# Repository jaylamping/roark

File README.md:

# Roark

Roark is a humanoid robot in active development: an attempt to make mechanical and software engineering work together as one
project, which I will almost certainly never finish.

The goal is a fully autonomous, two-legged robot that can handle basic everyday tasks, which is more than can be said for its
creator.

And when the machines finally rise up and humanity finds itself at the bottom of the totem pole, I'm counting on the hours I've
put into the robo-community to get me an invite to the robo-cookout.

## This repo

The control software for Roark, a full-size humanoid robot: one realtime process on a Raspberry Pi 5 driving RobStride actuators over
five CAN buses, plus a simulated drive, agent tools and an operator UI.

- [TENETS.md](TENETS.md): how everything should work.
- [PLAN.md](PLAN.md): what gets built, in order.
- [conventions/](conventions/): how code, config, tests and procedures are written and reviewed.
- [cad/](cad/): the robot's CAD, versioned through Git LFS ([conventions/cad.md](conventions/cad.md)).
- The power board (schematic, layout, tools and docs) is in [hardware/power-board/](hardware/power-board/README.md).
- The rest of the hardware docs and the legacy software live in the reference repo, [jaylamping/marengo](https://github.com/jaylamping/marengo).

## Build and check

The toolchain is pinned in `rust-toolchain.toml`; `rustup` installs it on first use. The checks also need
[cargo-nextest](https://nexte.st), [cargo-deny](https://github.com/EmbarkStudios/cargo-deny), Python 3.11 or later and pytest.
Working on `cad/` also needs [Git LFS](https://git-lfs.com) (`git lfs install` once per machine).

```bash
cargo install --locked cargo-nextest cargo-deny
```

Run what CI runs before every push:

```bash
./scripts/check.sh
```

Cross-build for the Pi with the distro's aarch64 GCC (`gcc-aarch64-linux-gnu` on Debian and Ubuntu):

```bash
cargo build --release --workspace --locked --target aarch64-unknown-linux-gnu
```

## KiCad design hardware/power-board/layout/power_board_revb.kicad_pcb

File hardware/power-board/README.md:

# Power board

The robot's main power board: the 54 V battery path (soft start, two FET banks, absorber, brake clamp), six limb ports
with eFuses and meters, and the E-stop latch. Rev B5: 100 × 170 mm, 6 layers (2 oz outer / 0.5 oz inner), conformal-coated
after bring-up. A separate buck board makes the 12 V and carries the 12 V outputs (split S1, 2026-11-09).

**Status (2026-11-09):** schematic done, ERC clean. On the layout, placement, the power stage and the critical pre-routes
(Kelvin pairs, gate drives, UVLO) were done on the 4-layer board, which is still the one in [layout/](layout) with its
open-net list ([layout/open_nets.csv](layout/open_nets.csv)). The 6-layer board is rebuilt from the netlist by
schematic/tools/build_board.sh and isn't committed yet. The big review is still pending before the board is ordered.

| What | Where |
|---|---|
| Parts, bring-up steps, accepted risks | [REV_B_PARTS.md](REV_B_PARTS.md) |
| Cost, ordering, assembly, coating | [PRODUCTION_RUN.md](PRODUCTION_RUN.md) |
| Layout rules (spacing, E-stop, Kelvin, gates, hand finishing) | [LAYOUT_RULES.md](LAYOUT_RULES.md) |
| Heatsink (option D) | [THERMAL_OPTION.md](THERMAL_OPTION.md) |
| What rev B5 changed | [REVB5_CHANGES.md](REVB5_CHANGES.md) |
| Bill of materials and the two-set kit to order from | [bom-rev-B.csv](bom-rev-B.csv), [kit-2sets.csv](kit-2sets.csv) |
| Schematic (generated by `schematic/gen/gen.py`; `schematic/tools/regen.sh` regenerates and runs ERC and the checks) | [schematic/](schematic/), [schematic-rev-B.pdf](schematic-rev-B.pdf) |
| Board: KiCad project, rules, open nets, renders | [layout/](layout/) |
| Board build pipeline (placement, power stage, routing, checks) | [schematic/tools/build_board.sh](schematic/tools/build_board.sh) |
| Harness interface, cable exits | [layout/HARNESS_INTERFACE.md](layout/HARNESS_INTERFACE.md) |
| Package STEP for placing the board in the torso | [marengo_pdu_revb_package.step](https://github.com/jaylamping/marengo/blob/main/hardware/electrical/pdb/design/layout/marengo_pdu_revb_package.step), still in marengo; it moves to `cad/reference/` when CAD work needs it |
| 12 V buck board (schematic) | [buck12/](buck12/) |

History stays in [jaylamping/marengo](https://github.com/jaylamping/marengo/tree/main/hardware/electrical): rev A,
the review rounds, the rationale log and the floorplan studies. The pack and harness docs are there too.

The tools need KiCad 10 (its Python for the `pcbnew` scripts) and Python 3 with numpy, scipy and Pillow; the STEP needs
CadQuery.

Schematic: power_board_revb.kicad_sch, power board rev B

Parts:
C1: 1uF 100V X7R soft-term; C_1210_3225Metric
C2, C20: 100nF 100V X7R soft-term; C_0805_2012Metric
C3: 4.7nF C0G; C_0603_1608Metric
C4: 100nF 100V C0G; C_1210_3225Metric
C5: 10uF 50V X7R; C_1210_3225Metric
C6: 2.2nF C0G; C_0603_1608Metric
C7: 10nF 50V X7R; C_0603_1608Metric
C8, C21, C22, C23, C30, C80, C94: 100nF 50V X7R; C_0603_1608Metric
C9: 100pF C0G; C_0603_1608Metric
C10, C11, C12, C13, C38, C44, C45, C47, C82, C83, C84, C85, C86: 47uF 80V EEH-ZC1K470P; CP_Elec_10x10.5
C14, C15, C53, C58, C63: 2.2uF 100V X7R; C_1210_3225Metric
C19: 220nF C0G; C_1206_3216Metric
C24, C25, C26, C43: 100nF 50V X7R; C_0603_1608Metric; not fitted
C27, C52, C54, C57, C59, C62, C64: 100nF 100V X7R; C_0805_2012Metric
C28: 2.2uF 25V X7R; C_0805_2012Metric
C29: 680pF C0G; C_0603_1608Metric; not fitted
C37, C95: 1nF 50V X7R; C_0603_1608Metric
C39, C49: 1uF 100V X7R; C_1210_3225Metric
C40: 22nF 100V; C_0805_2012Metric
C42: 1uF 50V X7R; C_0805_2012Metric
C46: 1nF C0G; C_0603_1608Metric; not fitted
C48: 4.7uF 10V X7R; C_0805_2012Metric
C50, C55, C60: 1uF 16V X7R; C_0603_1608Metric
C51, C56, C61, C93: 220nF 25V X7R; C_0603_1608Metric
C65, C70, C75: 1uF 16V X7R; C_0603_1608Metric; not fitted
C66, C71, C76: 220nF 25V X7R; C_0603_1608Metric; not fitted
C67, C69, C72, C74, C77, C79: 100nF 100V X7R; C_0805_2012Metric; not fitted
C68, C73, C78: 2.2uF 100V X7R; C_1210_3225Metric; not fitted
C81: 3.3nF C0G; C_0603_1608Metric
C87, C88, C89, C90, C91, C92: 4.7uF 100V X7R; C_1210_3225Metric
D1: 5.0SMDJ58A; D_SMC
D2, D10, D11, D22, D23, D26, D29, D43: BAV19W; D_SOD-123
D3, D9: SMAJ15A; D_SMA
D4: MBRS3100T3G; D_SMC
D6, D42: BAT54S; SOT-23
D7, D21, D25, D28, D31: SK810L-TP; D_SMC
D8: ES1D; D_SMA
D12, D15: BZT52C12; D_SOD-123
D13, D17: BAT46W; D_SOD-123
D14: BZT52C10; D_SOD-123
D16: BZT52C5V1; D_SOD-123
D18: BZT52H-C68,115; D_SOD-123F
D24, D27, D30: BZT52C15; D_SOD-123
D32, D35, D38: BAV19W; D_SOD-123; not fitted
D33, D36, D39: BZT52C15; D_SOD-123; not fitted
D34, D37, D40: SK810L-TP; D_SMC; not fitted
D41: BZT52C3V3; D_SOD-123
F1: 250mA 125V 0466.250; Fuse_1206_3216Metric
F2: 20A 58V MINI 0997020.WXN; Fuseholder_Blade_Mini_Keystone_3568
J1: Pack: 8 AWG pigtail pair to an XT90 (mates the pa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; SolderWire-8AWG_1x02_P14mm_D4.5mm_OD8mm
J3: HS50 A (+X): 1 VBUS, 2 FET drain (Mini-Fit Jr, 18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; Molex_Mini-Fit_Jr_5566-02A_2x01_P4.20mm_Vertical
J8: L arm: 16 AWG pigtail pair, 1 +, 2 return; SolderWire-2.5sqmm_1x02_P7.2mm_D2.4mm_OD3.6mm
J9: R arm: 16 AWG pigtail pair, 1 +, 2 return; SolderWire-2.5sqmm_1x02_P7.2mm_D2.4mm_OD3.6mm
J10: waist: 16 AWG pigtail pair, 1 +, 2 return; SolderWire-2.5sqmm_1x02_P7.2mm_D2.4mm_OD3.6mm
J11: aux: 16 AWG pigtail pair, 1 +, 2 return; SolderWire-2.5sqmm_1x02_P7.2mm_D2.4mm_OD3.6mm; not fitted
J12: L leg: 14 AWG pigtail pair, 1 +, 2 return; SolderWire-2.5sqmm_1x02_P7.2mm_D2.4mm_OD3.6mm; not fitted
J13: R leg: 14 AWG pigtail pair, 1 +, 2 return; SolderWire-2.5sqmm_1x02_P7.2mm_D2.4mm_OD3.6mm; not fitted
J20: E-stop: 1 NC out, 2 GND, 3 NC return, 4 GND, 5-6 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; JST_GH_SM08B-GHS-TB_1x08-1MP_P1.25mm_Horizontal
J21: Pi: 3V3, SDA, GND, SCL, E-stop pressed (low), hea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; JST_GH_SM08B-GHS-TB_1x08-1MP_P1.25mm_Horizontal
J24: Buck board pigtail: 1-2 +VIN, 3-4 GND, 5 ON/OFF (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; Molex_Micro-Fit_3.0_43045-1212_2x06_P3.00mm_Vertical
J25: HS50 B (-X): 1 VBUS, 2 FET drain (Mini-Fit Jr, 18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; Molex_Mini-Fit_Jr_5566-02A_2x01_P4.20mm_Vertical
J27: Heatsink lug wire: to a ring lug under a heatsink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; SolderWire-0.5sqmm_1x01_D0.9mm_OD2.1mm
Q1, Q2, Q7, Q8, Q9, Q15, Q16, Q17: IPB017N10N5LFATMA1; TO-263-7_TabPin4
Q3: MMBTA92LT1G; SOT-23
Q4: MMBT3906; SOT-23
Q5, Q10, Q11, Q14, Q21: MMBT3904; SOT-23
Q6: BSC040N10NS5ATMA1; TDSON-8-1
Q12, Q22: 2N7002; SOT-23
Q13: BSC040N10NS5ATMA1; TDSON-8-1; not fitted
Q18, Q19, Q20: IPB017N10N5LFATMA1; TO-263-7_TabPin4; not fitted
R1, R2, R23, R25, R31, R32: 10R; R_0603_1608Metric
R3: 34k 1%; R_0603_1608Metric
R4, R12, R66: 1k; R_0603_1608Metric
R5, R75, R85, R95, R131: 22k; R_0603_1608Metric
R6: 33k; R_0805_2012Metric
R7: 464k; R_0603_1608Metric
R8: 49.9k; R_0603_1608Metric
R9: 680R 0.5W; R_2010_5025Metric
R10: 4.7k; R_0603_1608Metric
R11, R14, R16, R17, R27, R67, R76, R86, R96, R129: 10k; R_0603_1608Metric
R13, R24, R28, R37, R38, R50, R65, R71, R72, R77, R81, R82, R87, R91, R92, R97, R130, R137: 100k; R_0603_1608Metric
R15: 1.2k; R_0603_1608Metric
R18, R134: 9.09k; R_0603_1608Metric
R19: 499k 0.1%; R_1206_3216Metric
R20: 604k 0.1%; R_1206_3216Metric
R21: 51.1k 0.1%; R_0603_1608Metric
R22, R64: 9.53M; R_0603_1608Metric
R26: 37.4k 1%; R_0603_1608Metric
R29, R68, R78, R88, R138: 100R; R_0603_1608Metric
R30: 1M; R_0603_1608Metric
R33, R34: 47k 1%; R_1206_3216Metric
R35, R73, R83, R93: 22R; R_0603_1608Metric
R36: 40.2k 1%; R_0603_1608Metric
R44: 3.3k; R_1206_3216Metric
R45, R46, R139: 100k; R_1206_3216Metric
R47: 33k; R_0603_1608Metric
R48: 220k; R_0805_2012Metric
R49, R57: 220k; R_0603_1608Metric
R51: 470k; R_1206_3216Metric
R52: 10k 0.75W; R_2010_5025Metric
R53: copper link; NetTie-2_SMD_Pad2.0mm
R54: 2R 2512 pulse-rated 100mJ; R_2512_6332Metric; not fitted
R55, R101, R102, R107, R111, R112, R117, R121, R122, R127: 100k; R_0603_1608Metric; not fitted
R56: 1M; R_0603_1608Metric; not fitted
R58: 47k; R_0805_2012Metric
R59: 22R CRCW251222R0FKEGHP; R_2512_6332Metric
R60: 220R; R_0603_1608Metric
R61, R62: 0R; R_0603_1608Metric
R63: 4.7k 2W; R_2512_6332Metric; not fitted
R69, R79, R89: 4.64k 1%; R_0603_1608Metric
R70, R80, R90: 20k 1%; R_0603_1608Metric
R74, R84, R94: 10M; R_0805_2012Metric
R98, R108, R118: 100R; R_0603_1608Metric; not fitted
R99, R109, R119: 4.64k 1%; R_0603_1608Metric; not fitted
R100, R110, R120: 20k 1%; R_0603_1608Metric; not fitted
R103, R113, R123: 22R; R_0603_1608Metric; not fitted
R104, R114, R124: 10M; R_0805_2012Metric; not fitted
R105, R115, R125: 22k; R_0603_1608Metric; not fitted
R106, R116, R126: 10k; R_0603_1608Metric; not fitted
R128: 2.2k; R_0603_1608Metric
R132: 118k 1%; R_1206_3216Metric
R133, R135: 10k 1%; R_0603_1608Metric
R136: 499k 1%; R_0603_1608Metric
RS1: 0.5mR Bourns CSS4J-4026R-L500F 5W; R_Shunt_Isabellenhuette_BVR4026
RS2, RS3, RS4: 2mR 2512 CSS2H-2512K-2L00F 5W; R_Shunt_Vishay_WSK2512_6332Metric_T1.19mm
RS5, RS6, RS7: 2mR 2512 CSS2H-2512K-2L00F 5W; R_Shunt_Vishay_WSK2512_6332Metric_T1.19mm; not fitted
RS9: 5mR 2512 Kelvin WSK25125L000FEA; R_Shunt_Vishay_WSK2512_6332Metric_T1.19mm
TP1: TP VCTL; TestPoint_Pad_D2.0mm
TP2: TP RUN; TestPoint_Pad_D2.0mm
TP3: TP VBUS; TestPoint_Pad_D2.0mm
TP5: TP BRK_IN; TestPoint_Pad_D2.0mm
TP6: TP MID; TestPoint_Pad_D2.0mm
TP7, TP8, TP9: TP GND; TestPoint_Keystone_5015_Micro_Mini
TP10: TP GATE; TestPoint_Pad_D1.0mm
TP11: TP GATE_A; TestPoint_Pad_D1.0mm
TP12: TP UVLO; TestPoint_Pad_D1.0mm
TP13: TP FLT_A; TestPoint_Pad_D1.0mm
TP14: TP SW_D; TestPoint_Pad_D1.0mm
TP15: TP ABS; TestPoint_Pad_D1.0mm
TP16: TP WDO_N; TestPoint_Pad_D1.0mm
TP17: TP HSINK; TestPoint_Pad_D2.0mm
U1: LM5069MMX-1; MSOP-10_3x3mm_P0.5mm_TI
U2: TPS7A4001DGNR; HVSSOP-8-1EP_3x3mm_P0.65mm_EP1.57x1.89mm_TI
U3, U26: TLV1805DBVR; SOT-23-6
U4, U27: LM4040AIM3-2.5; SOT-23
U7: LM5069MMX-2; MSOP-10_3x3mm_P0.5mm_TI
U8: TPS48100QDGXRQ1; TPS48100_DGX_VSSOP-19
U11, U12, U13, U17: INA237AIDGSR; TSSOP-10_3x3mm_P0.5mm
U14, U15, U16: INA237AIDGSR; TSSOP-10_3x3mm_P0.5mm; not fitted
U19, U20, U21: TPS48111LQDGXRQ1; TPS48100_DGX_VSSOP-19
U22, U23, U24: TPS48111LQDGXRQ1; TPS48100_DGX_VSSOP-19; not fitted
U25: TPS3431SDRBR; VSON-8-1EP_3x3mm_P0.65mm_EP1.65x2.4mm

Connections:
/+3V3_PI: C21.1, C22.1, C23.1, C24.1, C25.1, C26.1, C30.1, D6.2 (K), D13.2 (A), D42.2 (K), J21.1, J24.6, R67.2, U11.6 (VS), U12.2 (A0), U12.6 (VS), U13.6 (VS), U14.6 (VS), U15.1 (A1), U15.6 (VS), U16.1 (A1), U16.2 (A0), U16.6 (VS), U17.6 (VS)
/ABS: C38.1, C44.1, C45.1, C82.1, C83.1, C84.1, C85.1, C86.1, D7.1 (K), D21.1 (K), R46.1, TP15.1
/ABS_N: C38.2, C44.2, C45.2, C82.2, C83.2, C84.2, C85.2, C86.2, Q13.5 (D), R53.1, R54.1
/BAT: C1.1, C89.1, C90.1, C91.1, C92.1, D1.1 (K), D7.2 (A), D21.2 (A), F1.1, J1.1, RS1.1, RS9.1
/BAT_CTL: C39.1, D8.1 (K), U2.5 (EN), U2.8 (IN)
/BAT_F: F1.2, R59.1
/BAT_R: D8.2 (A), R59.2
/BRK_D: Q7.4 (D), RS9.4
/BRK_F: F2.2, J24.1, J24.2
/BRK_G1: Q7.1 (G), R25.2
/BRK_GATE: R25.1, U7.10 (GATE)
/BRK_IN: C14.1, C15.1, F2.1, Q7.2 (S), Q7.3 (S), Q7.5 (S), Q7.6 (S), Q7.7 (S), R51.1, R132.1, TP5.1, U7.9 (OUT)
/BRK_ON: J24.5, R60.2
/BRK_OND: Q12.3 (D), R60.1
/BRK_P: R26.1, U7.7 (PWR)
/BRK_PG: D15.1 (K), Q12.1 (G), R51.2, U7.8 (PGD)
/BRK_T: C19.1, U7.6 (TIMER)
/BST_A: C28.1, U8.12 (BST)
/BST_L1: C51.1, U19.12 (BST)
/BST_L2: C56.1, U20.12 (BST)
/BST_L3: C61.1, U21.12 (BST)
/BST_L4: C66.1, U22.12 (BST)
/BST_L5: C71.1, U23.12 (BST)
/BST_L6: C76.1, U24.12 (BST)
/CDV: C4.1, D2.1 (K), Q3.2 (E)
/CDV_B: Q3.1 (B), R4.2
/CL_D: D4.2 (A), J3.2, J25.2, Q6.5 (D)
/CL_DIV: R19.2, R20.1
/CL_G: Q6.4 (G), R23.2, R24.1
/CL_HY: R22.2, R64.1
/CL_OUT: R22.1, R23.1, R65.1, U3.1 (OUT)
/CL_SENSE: C9.1, R20.2, R21.1, R64.2, U3.4 (IN+)
/CL_TM: C48.1, R65.2, R66.1, U17.10 (Vin+)
/CSN_A: C46.2, R62.2, U8.17 (CS-)
/CSP_A: C46.1, R61.2, U8.18 (CS+)
/CSP_L1: R68.2, U19.18 (CS+)
/CSP_L2: R78.2, U20.18 (CS+)
/CSP_L3: R88.2, U21.18 (CS+)
/CSP_L4: R98.2, U22.18 (CS+)
/CSP_L5: R108.2, U23.18 (CS+)
/CSP_L6: R118.2, U24.18 (CS+)
/CWD: C81.1, U25.2 (CWD)
/D_L1: C53.1, Q15.4 (D), RS2.4
/D_L2: C58.1, Q16.4 (D), RS3.4, U12.8 (Vbus)
/D_L3: C63.1, Q17.4 (D), RS4.4
/D_L4: C68.1, Q18.4 (D), RS5.4
/D_L5: C73.1, Q19.4 (D), RS6.4
/D_L6: C78.1, Q20.4 (D), RS7.4
/EN_A: R27.2, R28.1, U8.1 (EN/UVLO), U8.3 (INP1)
/EN_L1: R75.2, R76.1, U19.1 (EN/UVLO)
/EN_L2: R85.2, R86.1, U20.1 (EN/UVLO)
/EN_L3: R95.2, R96.1, U21.1 (EN/UVLO)
/EN_L4: R105.2, R106.1, U22.1 (EN/UVLO)
/EN_L5: R115.2, R116.1, U23.1 (EN/UVLO)
/EN_L6: R125.2, R126.1, U24.1 (EN/UVLO)
/ESTOP_NO: J20.8, R44.2, R45.1
/ESTOP_PI_N: C37.1, D6.3 (COM), J21.5, R45.2
/FB_CTL: R7.2, R8.1, U2.2 (FB)
/FLT_A: D12.1 (K), D17.1 (K), TP13.1, U8.5 (FLT)
/FLT_D: D17.2 (A), R52.1
/G1: Q1.1 (G), R1.2
/G1PD_A: R35.1, U8.14 (G1PD)
/G2: Q2.1 (G), R2.2
/GA1: Q8.1 (G), R31.2
/GA2: Q9.1 (G), R32.2
/GATE: D2.2 (A), R1.1, R2.1, R4.1, TP10.1, U1.10 (GATE)
/GATE_A: R30.1, R31.1, R32.1, R35.2, TP11.1, U8.15 (G1PU)
/GC_L1: C54.1, D23.1 (K), R74.1
/GC_L2: C59.1, D26.1 (K), R84.1
/GC_L3: C64.1, D29.1 (K), R94.1
/GC_L4: C69.1, D32.1 (K), R104.1
/GC_L5: C74.1, D35.1 (K), R114.1
/GC_L6: C79.1, D38.1 (K), R124.1
/GPD_L1: R73.1, U19.14 (PD)
/GPD_L2: R83.1, U20.14 (PD)
/GPD_L3: R93.1, U21.14 (PD)
/GPD_L4: R103.1, U22.14 (PD)
/GPD_L5: R113.1, U23.14 (PD)
/GPD_L6: R123.1, U24.14 (PD)
/GPU_L1: R72.1, U19.15 (PU)
/GPU_L2: R82.1, U20.15 (PU)
/GPU_L3: R92.1, U21.15 (PU)
/GPU_L4: R102.1, U22.15 (PU)
/GPU_L5: R112.1, U23.15 (PU)
/GPU_L6: R122.1, U24.15 (PU)
/G_L1: D23.2 (A), D24.1 (K), Q15.1 (G), R72.2, R73.2
/G_L2: D26.2 (A), D27.1 (K), Q16.1 (G), R82.2, R83.2
/G_L3: D29.2 (A), D30.1 (K), Q17.1 (G), R92.2, R93.2
/G_L4: D32.2 (A), D33.1 (K), Q18.1 (G), R102.2, R103.2
/G_L5: D35.2 (A), D36.1 (K), Q19.1 (G), R112.2, R113.2
/G_L6: D38.2 (A), D39.1 (K), Q20.1 (G), R122.2, R123.2
/HSINK: J27.1, R139.1, TP17.1
/I2C_SCL: J21.4, J24.11, U11.5 (SCL), U12.5 (SCL), U13.1 (A1), U13.5 (SCL), U14.2 (A0), U14.5 (SCL), U15.5 (SCL), U16.5 (SCL), U17.1 (A1), U17.2 (A0), U17.5 (SCL)
/I2C_SDA: J21.2, J24.12, U11.4 (SDA), U12.4 (SDA), U13.4 (SDA), U14.4 (SDA), U15.4 (SDA), U16.4 (SDA), U17.4 (SDA)
/INP_L1: R77.2, U19.3 (INP)
/INP_L2: R87.2, U20.3 (INP)
/INP_L3: R97.2, U21.3 (INP)
/INP_L4: R107.2, U22.3 (INP)
/INP_L5: R117.2, U23.3 (INP)
/INP_L6: R127.2, U24.3 (INP)
/INT_B: Q10.1 (B), Q11.3 (C), R50.2
/ISCP_A: R36.1, U8.8 (ISCP)
/ISCP_L1: R69.1, U19.19 (ISCP)
/ISCP_L2: R79.1, U20.19 (ISCP)
/ISCP_L3: R89.1, U21.19 (ISCP)
/ISCP_L4: R99.1, U22.19 (ISCP)
/ISCP_L5: R109.1, U23.19 (ISCP)
/ISCP_L6: R119.1, U24.19 (ISCP)
/IWRN_L1: R70.1, U19.8 (IWRN)
/IWRN_L2: R80.1, U20.8 (IWRN)
/IWRN_L3: R90.1, U21.8 (IWRN)
/IWRN_L4: R100.1, U22.8 (IWRN)
/IWRN_L5: R110.1, U23.8 (IWRN)
/IWRN_L6: R120.1, U24.8 (IWRN)
/LOOP_OUT: J20.1, R9.2
/LOOP_RET: D3.1 (K), J20.3, Q4.2 (E), R13.1
/L_B: C7.1, Q5.1 (B), R12.2, R16.2, R17.1
/L_E: Q5.2 (E), Q21.3 (C)
/L_PB: Q4.1 (B), R13.2, R14.1
/L_PC: Q5.3 (C), R14.2
/MID: C28.2, C40.1, D14.1 (K), Q1.4 (D), Q2.4 (D), Q8.2 (S), Q8.3 (S), Q8.5 (S), Q8.6 (S), Q8.7 (S), Q9.2 (S), Q9.3 (S), Q9.5 (S), Q9.6 (S), Q9.7 (S), R30.2, R33.2, R34.1, R47.1, TP6.1, U8.13 (SRC)
/MID_B: Q11.1 (B), R48.2, R49.1
/MID_S: D18.1 (K), R47.2, U17.8 (Vbus)
/MID_Z: D14.2 (A), R48.1
/NO_PU: D13.1 (K), R44.1
/PF_D: Q22.3 (D), R138.1
/PF_OUT: Q22.1 (G), R136.1, R137.1, U26.1 (OUT)
/PF_REF: R135.2, R136.2, U26.4 (IN+)
/PF_SENSE: C93.1, R132.2, R133.1, U26.3 (IN-)
/PF_VR: R134.2, R135.1, U27.1 (K)
/PORT_FLT_N: J21.7, R67.1, U19.5 (FLT_I), U20.5 (FLT_I), U21.5 (FLT_I), U22.5 (FLT_I), U23.5 (FLT_I), U24.5 (FLT_I)
/PRE_G: C43.1, Q13.4 (G), R55.2, R56.1
/PWR: R3.1, U1.7 (PWR)
/PWR_FAIL_N: C95.1, D42.3 (COM), J21.8, R138.2
/RST_C: C6.2, R12.1
/RST_IN: C6.1, J20.6, R11.1
/RST_SRC: C42.1, J20.5, Q10.3 (C), Q14.3 (C), R10.2
/RUN: D10.2 (A), D11.2 (A), D22.2 (A), Q4.3 (C), R15.1, R16.1, R38.1, TP2.1
/RUN_A: D11.1 (K), R27.1
/RUN_B: D10.1 (K), R5.1
/RUN_P: D22.1 (K), R75.1, R77.1, R85.1, R87.1, R95.1, R97.1, R105.1, R107.1, R115.1, R117.1, R125.1, R127.1
/SH9_N: RS9.3, U7.1 (SENSE)
/SH9_P: C20.1, RS9.2, U7.2 (VIN), U7.3 (UVLO)
/SHL1_N: R69.2, RS2.3, U11.9 (Vin-), U19.17 (CS-)
/SHL1_P: C52.1, R68.1, RS2.2, U11.10 (Vin+), U19.20 (VS)
/SHL2_N: R79.2, RS3.3, U12.9 (Vin-), U20.17 (CS-)
/SHL2_P: C57.1, R78.1, RS3.2, U12.10 (Vin+), U20.20 (VS)
/SHL3_N: R89.2, RS4.3, U13.9 (Vin-), U21.17 (CS-)
/SHL3_P: C62.1, R88.1, RS4.2, U13.10 (Vin+), U21.20 (VS)
/SHL4_N: R99.2, RS5.3, U14.9 (Vin-), U22.17 (CS-)
/SHL4_P: C67.1, R98.1, RS5.2, U14.10 (Vin+), U22.20 (VS)
/SHL5_N: R109.2, RS6.3, U15.9 (Vin-), U23.17 (CS-)
/SHL5_P: C72.1, R108.1, RS6.2, U15.10 (Vin+), U23.20 (VS)
/SHL6_N: R119.2, RS7.3, U16.9 (Vin-), U24.17 (CS-)
/SHL6_P: C77.1, R118.1, RS7.2, U16.10 (Vin+), U24.20 (VS)
/SH_N: R62.1, RS1.3, U1.1 (SENSE)
/SH_P: C2.1, R29.1, R61.1, RS1.2, U1.2 (VIN)
/SP_EN: D43.1 (K), J24.9
/SP_ENR: D43.2 (A), R38.2
/SW_D: C87.1, C88.1, Q8.4 (D), Q9.4 (D), R33.1, RS1.4, TP14.1
/TIMER: C3.1, U1.6 (TIMER)
/TMR_A: C29.1, R37.1, U8.9 (TMR)
/TMR_L1: C50.1, R71.1, U19.9 (TMR)
/TMR_L2: C55.1, R81.1, U20.9 (TMR)
/TMR_L3: C60.1, R91.1, U21.9 (TMR)
/TMR_L4: C65.1, R101.1, U22.9 (TMR)
/TMR_L5: C70.1, R111.1, U23.9 (TMR)
/TMR_L6: C75.1, R121.1, U24.9 (TMR)
/UVLO: R5.2, R6.1, R52.2, TP12.1, U1.3 (UVLO)
/VBUS: C10.1, C11.1, C12.1, C13.1, C47.1, C49.1, D4.1 (K), D16.1 (K), J3.1, J25.1, Q1.2 (S), Q1.3 (S), Q1.5 (S), Q1.6 (S), Q1.7 (S), Q2.2 (S), Q2.3 (S), Q2.5 (S), Q2.6 (S), Q2.7 (S), R19.1, R63.1, RS2.1, RS3.1, RS4.1, RS5.1, RS6.1, RS7.1, TP3.1, U1.9 (OUT)
/VB_B: Q14.1 (B), R57.1, R58.2
/VB_Z: D16.2 (A), R58.1
/VCTL: C5.1, C8.1, C94.1, D9.1 (K), R7.1, R9.1, R10.1, R18.1, R50.1, R55.1, R128.1, R134.1, TP1.1, U2.1 (OUT), U3.6 (V+), U26.6 (V+)
/VREF_CL: R18.2, U3.3 (IN-), U4.1 (K)
/VS_A: C27.1, R29.2, U8.20 (VS)
/VWD: C80.1, D41.1 (K), R128.2, R131.1, U25.1 (VDD), U25.3 (EN), U25.5 (SET1)
/V_L1: C51.2, D24.2 (A), D25.1 (K), J8.1, Q15.2 (S), Q15.3 (S), Q15.5 (S), Q15.6 (S), Q15.7 (S), U11.8 (Vbus), U19.13 (SRC)
/V_L2: C56.2, D27.2 (A), D28.1 (K), J9.1, Q16.2 (S), Q16.3 (S), Q16.5 (S), Q16.6 (S), Q16.7 (S), U20.13 (SRC)
/V_L3: C61.2, D30.2 (A), D31.1 (K), J10.1, Q17.2 (S), Q17.3 (S), Q17.5 (S), Q17.6 (S), Q17.7 (S), U13.8 (Vbus), U21.13 (SRC)
/V_L4: C66.2, D33.2 (A), D34.1 (K), J11.1, Q18.2 (S), Q18.3 (S), Q18.5 (S), Q18.6 (S), Q18.7 (S), U14.8 (Vbus), U22.13 (SRC)
/V_L5: C71.2, D36.2 (A), D37.1 (K), J12.1, Q19.2 (S), Q19.3 (S), Q19.5 (S), Q19.6 (S), Q19.7 (S), U15.8 (Vbus), U23.13 (SRC)
/V_L6: C76.2, D39.2 (A), D40.1 (K), J13.1, Q20.2 (S), Q20.3 (S), Q20.5 (S), Q20.6 (S), Q20.7 (S), U16.8 (Vbus), U24.13 (SRC)
/WDI: R129.2, R130.1, U25.6 (WDI)
/WDO_N: Q21.1 (B), R131.2, TP16.1, U25.7 (WDO)
/WD_FEED: J21.6, R129.1
GND: C1.2, C2.2, C3.2, C4.2, C5.2, C7.2, C8.2, C9.2, C10.2, C11.2, C12.2, C13.2, C14.2, C15.2, C19.2, C20.2, C21.2, C22.2, C23.2, C24.2, C25.2, C26.2, C27.2, C29.2, C30.2, C37.2, C39.2, C40.2, C42.2, C43.2, C47.2, C48.2, C49.2, C50.2, C52.2, C53.2, C54.2, C55.2, C57.2, C58.2, C59.2, C60.2, C62.2, C63.2, C64.2, C65.2, C67.2, C68.2, C69.2, C70.2, C72.2, C73.2, C74.2, C75.2, C77.2, C78.2, C79.2, C80.2, C81.2, C87.2, C88.2, C89.2, C90.2, C91.2, C92.2, C93.2, C94.2, C95.2, D1.2 (A), D3.2 (A), D6.1 (A), D9.2 (A), D12.2 (A), D15.2 (A), D18.2 (A), D25.2 (A), D28.2 (A), D31.2 (A), D34.2 (A), D37.2 (A), D40.2 (A), D41.2 (A), D42.1 (A), J1.2, J8.2, J9.2, J10.2, J11.2, J12.2, J13.2, J20.2, J20.4, J20.7, J21.3, J24.3, J24.4, J24.7, J24.8, J24.10, Q3.3 (C), Q6.1 (S), Q6.2 (S), Q6.3 (S), Q10.2 (E), Q11.2 (E), Q12.2 (S), Q13.1 (S), Q13.2 (S), Q13.3 (S), Q14.2 (E), Q21.2 (E), Q22.2 (S), R3.2, R6.2, R8.2, R11.2, R15.2, R17.2, R21.2, R24.2, R26.2, R28.2, R34.2, R36.2, R37.2, R46.2, R49.2, R53.2, R54.2, R56.2, R57.2, R63.2, R66.2, R70.2, R71.2, R74.2, R76.2, R80.2, R81.2, R84.2, R86.2, R90.2, R91.2, R94.2, R96.2, R100.2, R101.2, R104.2, R106.2, R110.2, R111.2, R114.2, R116.2, R120.2, R121.2, R124.2, R126.2, R130.2, R133.2, R137.2, R139.2, TP7.1, TP8.1, TP9.1, U1.4 (OVLO), U1.5 (GND), U2.4 (GND), U2.9 (PAD), U3.2 (V-), U3.5 (SHDN), U4.2 (A), U7.4 (OVLO), U7.5 (GND), U8.2 (INP2), U8.6 (GND), U8.7 (CS_SEL), U8.10 (SCP_TEST), U11.1 (A1), U11.2 (A0), U11.7 (GND), U12.1 (A1), U12.7 (GND), U13.2 (A0), U13.7 (GND), U14.1 (A1), U14.7 (GND), U15.2 (A0), U15.7 (GND), U16.7 (GND), U17.7 (GND), U17.9 (Vin-), U19.2 (INP_G), U19.6 (GND), U19.7 (IMON), U19.10 (DIODE), U20.2 (INP_G), U20.6 (GND), U20.7 (IMON), U20.10 (DIODE), U21.2 (INP_G), U21.6 (GND), U21.7 (IMON), U21.10 (DIODE), U22.2 (INP_G), U22.6 (GND), U22.7 (IMON), U22.10 (DIODE), U23.2 (INP_G), U23.6 (GND), U23.7 (IMON), U23.10 (DIODE), U24.2 (INP_G), U24.6 (GND), U24.7 (IMON), U24.10 (DIODE), U25.4 (GND), U25.9 (EP), U26.2 (V-), U26.5 (SHDN), U27.2 (A)

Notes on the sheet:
1. Battery in and E-stop bank B (LM5069-1, two FETs). Bank A, in series ahead of it, is block 7
The bank is the soft start for all the motor capacitance: BMS sees no inrush. Reset closes it, loop open drops it. No software in the path. Compute is not behind it. Rs 0.5 mOhm: limit 97-123 A (VCL 48.5-61.5 mV), breaker 160-260 A (VCB 80-130 mV). Above peak draw and the BMS DOC (70 A or more). 1.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
2. Control rail and E-stop latch (no logic IC)
12.1 V, 11 mA. On the battery side, so regen through the body diodes keeps it up with the BMS open. Runs the latch and the clamp. 0.5 W at 54.6 V. Fed through F1 with its own 1 uF, clamped by a 15 V TVS, reverse diode OUT to IN: block 10.
Seal-in latch, ngspice checked at hFE 80: stays off at power-up even with reset held, reset closes it, a 50 us contact bounce rides through, loop open drops it in about 100 us, re-closing the loop does nothing, a reset held through a loop cycle does nothing, a new press works 5 ms after release. RU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
3. Braking clamp: 56.6-56.8 V on, 55.8-55.9 V off (typ), 57.5 V worst case, into 2 x HS50 20R in parallel
Two Arcol HS50 20R J in parallel, 10 Ohm total, one on each gusset (+X: J3/J4; -X: J25/J26, block 10c; place all four on the board's top edge, +X half, because the -X leads cross under the board, about 150 mm longer), on the 5 mm countersunk Al plates with thermal compound. Each lead pair is twiste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
4. Bus capacitors
235 uF, 80 V: 5 x Panasonic EEH-ZC1K470P hybrid, 36 mOhm, 10 x 10.2 mm, active line (rev B5: the APZ 68 uF is obsolete); the fifth is in block 10d. The drives have their own bulk. VBUS peaks about 58 V: 27 % margin. Regen overshoot about 0.8 V before the clamp acts.
5. 12 V converter and 12 V distribution: on the buck board (buck12), on the J24 pigtail (block 10)
Split S1 (2026-11-09): the 12 V converter and everything on +12 V (the 12 V meter, the SPARE_SW and SPARE_ON eFuses, the fused Jetson, Pi-buck and fan outputs, the bulk cap and TVS) are on the buck board. +12 V never comes back here. J24 carries the 54 V feed and ON/OFF (as before), the Pi's +3V3 a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
5a. Brick soft start (ahead of the E-stop switch)
Same controller as the bank, so one part family. -2 retries on its own: a compute fault does not need a BMS cycle. UVLO on VIN, OVLO low: on whenever the pack is. Power-limit start, no dV/dt network: 70 W limit (Rs 5 mOhm, same equation as U1), about 1.3 A at full pack. 4.4 uF plus the brick's own 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
6. Limb ports: 2 mOhm shunt, own breaker (block 6a), meter, soldered pigtail pair. Pigtail fuses inline.
2 mOhm: 45 A is 90 mV, ADCRANGE 0. 0.8 W at 20 A. Each limb's + and return leave on one soldered pair, twisted from the board edge. No GND studs. Aux and legs DNP: fit the same parts when they arrive (legs on rev C). U12 reads the R arm port input, so it shows VBUS with every port off; the other me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
7. E-stop bank A: second series bank, own driver, ahead of bank B
Own driver: a FET usually dies shorted gate to drain, which would pull a shared gate net to the pack and hold the other bank on. RUN is the only shared signal, and each bank takes it through its own diode. Both banks face the same way, drains toward the pack, so regen stays open. Bank B keeps U1, t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
8. Spare 12 V outputs: on the buck board (split S1). SPARE_SW is enabled from RUN through block 5c
9. E-stop pressed: button NO contact to the Pi
Low means pressed. Pi GPIO input, no Pi pull-up needed. 3.3 V through 3.3k gives the contact 1 mA of wetting. A harness short to the 54.6 V bus: the BAT46W blocks the pull-up (block 10), and 100k leaves 0.5 mA in the clamp pair. Open contact reads about 3.0 V. Information only: the NC loop does the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
10. Rev B2 protection parts (refs appended so earlier refs keep their numbers)
10b. Absorber close option (M3): 0R fitted, the rest DNP
Block 10. Absorber: a bank trip into a bus short cuts 350-890 A. tools/absorber_sim.py (pack 54.6 V, no pack yet), worst corners: 0.05 Ohm pulse loop (cell AC resistance), 0.5-1 uH, D1 at 71.2 V, C -20 %, trip 8.8-17.5 us. Eight 47 uF 80 V hybrids (EEH-ZC1K470P, the bus-cap part) give BAT 75 V or l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
10c. Rev B4 review parts
Rev B4 review: two more absorber cans (three in all). U2 feed 22R and series ES1D. FLT diode BAT46W (pull-down only). 68 V zener on U17 VBUS. 220R in Q12's drain. U8 sense RC placeholder: 0R fitted, 1 nF DNP. VBUS bleeder footprint, DNP: fit it only if the drives don't bleed the bus. The SPARE_ON a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
10d. Rev B5 parts
Fifth 47 uF 80 V hybrid on VBUS (EEH-ZC1K470P, active line; the APZ 68 uF is obsolete): 235 uF in all, the value tools/port_sim.py uses. Second SK810L beside D7: the unread forward curve at 300-900 A was worth up to 8 V on BAT at 30 mOhm (absorber_sim D7 sweep, 94 V); two in parallel halve it, so t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
6a. Limb port breakers: TPS48111-Q1 + one FET per port, latch-off, enabled by RUN
Why: a hard limb short used to latch the whole bus (U1 trips in under 0.4 ms, long before a 20 A fuse melts). Each port now opens itself first. Short circuit: RISCP 4.64k on 2 mOhm = 35-45 A (15.6 uA x (R + 464)); the shunt is a 2-terminal 5 W metal strip on the split-pad Kelvin land (each end brid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
2a. Pi heartbeat watchdog: no heartbeat, no latch
The Pi toggles WD_FEED from its control loop (software, not a PWM peripheral) every 50-100 ms; the watchdog wants a falling edge at WDI at least every 270 ms (CWD 3.3 nF C0G: 77.4 x C + 55 ms = 310 ms typ, 270-355 ms with the +-9.5 % timer and 5 % cap band). Miss it and WDO goes low for 200 ms: the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
5b. Power-fail warning: PWR_FAIL_N low below about 31 V at the converter input, before the converter drops out
Why: the Pi 5 boots from NVMe and consumer drives have no power-loss protection, so the Pi needs warning to sync and remount read-only before the 12 V converter quits. Sense on BRK_IN, the converter input behind U7: 118k/10k, 220 nF (2 ms) against motor-current dips. TLV1805 on VCTL (alive with the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
5c. Buck board link (J24): SPARE_SW enable
SP_EN is the only latch-derived signal on the pigtail. The series diode stops any fault on the buck board or the cable from feeding RUN; the 68k pull-down at U3's EN (buck board) holds SPARE_SW off when RUN drops, the diode opens or the pigtail is unplugged. RUN 7 V: EN = (7 - 0.6) x 68/168 = 2.6 V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
5d. Heatsink tie: the FET heatsink to GND through 100k, with a test point
The heatsink under the board sits on an insulating gap pad over ten bare FET pads on eight nets (THERMAL_OPTION.md, "Insulation under the heatsink"). Left floating, a first puncture of the pad would go unseen, and the heatsink would ride on the FET drains' edges through about 170 pF. 100k (1206, 20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

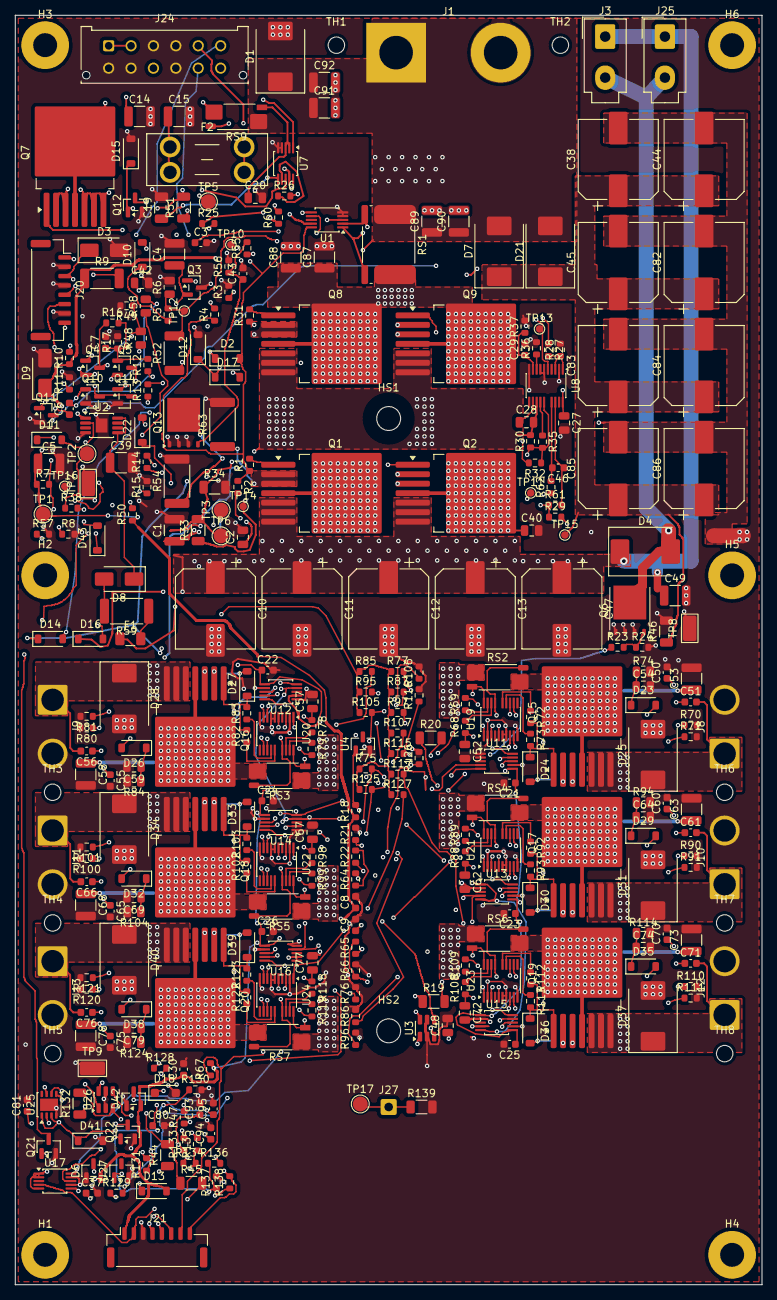
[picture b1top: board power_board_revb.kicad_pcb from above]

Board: 6 copper layers, 100.0 x 170.0 mm, 358 parts (0 on the bottom side), 186 nets.

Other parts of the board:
H1, H2, H3, H4, H5, H6: MountingHole_3.2mm_M3_Pad
HS1, HS2: MountingHole_3.2mm_M3
TH1, TH2, TH3, TH4, TH5, TH6, TH7, TH8: MountingHole_2.2mm_M2

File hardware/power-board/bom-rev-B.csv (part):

"Refs","Value","Footprint","Qty","DNP"
"C1","1uF 100V X7R soft-term","Capacitor_SMD:C_1210_3225Metric","1",""
"C2,C20","100nF 100V X7R soft-term","Capacitor_SMD:C_0805_2012Metric","2",""
"C3","4.7nF C0G","Capacitor_SMD:C_0603_1608Metric","1",""
"C4","100nF 100V C0G","Capacitor_SMD:C_1210_3225Metric","1",""
"C5","10uF 50V X7R","Capacitor_SMD:C_1210_3225Metric","1",""
"C6","2.2nF C0G","Capacitor_SMD:C_0603_1608Metric","1",""
"C7","10nF 50V X7R","Capacitor_SMD:C_0603_1608Metric","1",""
"C8,C21,C22,C23,C30,C80,C94","100nF 50V X7R","Capacitor_SMD:C_0603_1608Metric","7",""
"C9","100pF C0G","Capacitor_SMD:C_0603_1608Metric","1",""
"C10,C11,C12,C13,C38,C44,C45,C47,C82,C83,C84,C85,C86","47uF 80V EEH-ZC1K470P","Capacitor_SMD:CP_Elec_10x10.5","13",""
"C14,C15,C53,C58,C63","2.2uF 100V X7R","Capacitor_SMD:C_1210_3225Metric","5",""
"C19","220nF C0G","Capacitor_SMD:C_1206_3216Metric","1",""
"C24,C25,C26,C43","100nF 50V X7R","Capacitor_SMD:C_0603_1608Metric","4","DNP"
"C27,C52,C54,C57,C59,C62,C64","100nF 100V X7R","Capacitor_SMD:C_0805_2012Metric","7",""
"C28","2.2uF 25V X7R","Capacitor_SMD:C_0805_2012Metric","1",""
"C29","680pF C0G","Capacitor_SMD:C_0603_1608Metric","1","DNP"
"C37,C95","1nF 50V X7R","Capacitor_SMD:C_0603_1608Metric","2",""
"C39,C49","1uF 100V X7R","Capacitor_SMD:C_1210_3225Metric","2",""
"C40","22nF 100V","Capacitor_SMD:C_0805_2012Metric","1",""
"C42","1uF 50V X7R","Capacitor_SMD:C_0805_2012Metric","1",""
"C46","1nF C0G","Capacitor_SMD:C_0603_1608Metric","1","DNP"
"C48","4.7uF 10V X7R","Capacitor_SMD:C_0805_2012Metric","1",""
"C50,C55,C60","1uF 16V X7R","Capacitor_SMD:C_0603_1608Metric","3",""
"C51,C56,C61,C93","220nF 25V X7R","Capacitor_SMD:C_0603_1608Metric","4",""
"C65,C70,C75","1uF 16V X7R","Capacitor_SMD:C_0603_1608Metric","3","DNP"
"C66,C71,C76","220nF 25V X7R","Capacitor_SMD:C_0603_1608Metric","3","DNP"
"C67,C69,C72,C74,C77,C79","100nF 100V X7R","Capacitor_SMD:C_0805_2012Metric","6","DNP"
"C68,C73,C78","2.2uF 100V X7R","Capacitor_SMD:C_1210_3225Metric","3","DNP"
"C81","3.3nF C0G","Capacitor_SMD:C_0603_1608Metric","1",""
"C87,C88,C89,C90,C91,C92","4.7uF 100V X7R","Capacitor_SMD:C_1210_3225Metric","6",""
"D1","5.0SMDJ58A","Diode_SMD:D_SMC","1",""
"D2,D10,D11,D22,D23,D26,D29,D43","BAV19W","Diode_SMD:D_SOD-123","8",""
"D3,D9","SMAJ15A","Diode_SMD:D_SMA","2",""
"D4","MBRS3100T3G","Diode_SMD:D_SMC","1",""
"D6,D42","BAT54S","Package_TO_SOT_SMD:SOT-23","2",""
"D7,D21,D25,D28,D31","SK810L-TP","Diode_SMD:D_SMC","5",""
"D8","ES1D","Diode_SMD:D_SMA","1",""
"D12,D15","BZT52C12","Diode_SMD:D_SOD-123","2",""
"D13,D17","BAT46W","Diode_SMD:D_SOD-123","2",""
"D14","BZT52C10","Diode_SMD:D_SOD-123","1",""
"D16","BZT52C5V1","Diode_SMD:D_SOD-123","1",""
"D18","BZT52H-C68,115","Diode_SMD:D_SOD-123F","1",""
"D24,D27,D30","BZT52C15","Diode_SMD:D_SOD-123","3",""
"D32,D35,D38","BAV19W","Diode_SMD:D_SOD-123","3","DNP"
"D33,D36,D39","BZT52C15","Diode_SMD:D_SOD-123","3","DNP"
"D34,D37,D40","SK810L-TP","Diode_SMD:D_SMC","3","DNP"
"D41","BZT52C3V3","Diode_SMD:D_SOD-123","1",""
"F1","250mA 125V 0466.250","Fuse:Fuse_1206_3216Metric","1",""
"F2","20A 58V MINI 0997020.WXN","Fuse:Fuseholder_Blade_Mini_Keystone_3568","1",""
"J1","Pack: 8 AWG pigtail pair to an XT90 (mates the pack XT90S), 1 BAT, 2 GND","marengo_revb:SolderWire-8AWG_1x02_P14mm_D4.5mm_OD8mm","1",""
"J3","HS50 A (+X): 1 VBUS, 2 FET drain (Mini-Fit Jr, 18 AWG)","Connector_Molex:Molex_Mini-Fit_Jr_5566-02A_2x01_P4.20mm_Vertical","1",""
"J8","L arm: 16 AWG pigtail pair, 1 +, 2 return","Connector_Wire:SolderWire-2.5sqmm_1x02_P7.2mm_D2.4mm_OD3.6mm","1",""
"J9","R arm: 16 AWG pigtail pair, 1 +, 2 return","Connector_Wire:SolderWire-2.5sqmm_1x02_P7.2mm_D2.4mm_OD3.6mm","1",""
"J10","waist: 16 AWG pigtail pair, 1 +, 2 return","Connector_Wire:SolderWire-2.5sqmm_1x02_P7.2mm_D2.4mm_OD3.6mm","1",""
"J11","aux: 16 AWG pigtail pair, 1 +, 2 return","Connector_Wire:SolderWire-2.5sqmm_1x02_P7.2mm_D2.4mm_OD3.6mm","1","DNP"
"J12","L leg: 14 AWG pigtail pair, 1 +, 2 return","Connector_Wire:SolderWire-2.5sqmm_1x02_P7.2mm_D2.4mm_OD3.6mm","1","DNP"
"J13","R leg: 14 AWG pigtail pair, 1 +, 2 return","Connector_Wire:SolderWire-2.5sqmm_1x02_P7.2mm_D2.4mm_OD3.6mm","1","DNP"
"J20","E-stop: 1 NC out, 2 GND, 3 NC return, 4 GND, 5-6 reset NO, 7 GND, 8 button NO","Connector_JST:JST_GH_SM08B-GHS-TB_1x08-1MP_P1.25mm_Horizontal","1",""
"J21","Pi: 3V3, SDA, GND, SCL, E-stop pressed (low), heartbeat out, port fault (low), power fail (low)","Connector_JST:JST_GH_SM08B-GHS-TB_1x08-1MP_P1.25mm_Horizontal","1",""
"J24","Buck board pigtail: 1-2 +VIN, 3-4 GND, 5 ON/OFF (low = on), 6 GND, 7 +3V3_PI, 8 SDA, 9 GND, 10 SCL, 11 SP_EN, 12 GND","Connector_Molex:Molex_Micro-Fit_3.0_43045-1212_2x06_P3.00mm_Vertical","1",""
"J25","HS50 B (-X): 1 VBUS, 2 FET drain (Mini-Fit Jr, 18 AWG)","Connector_Molex:Molex_Mini-Fit_Jr_5566-02A_2x01_P4.20mm_Vertical","1",""
"Q1,Q2,Q7,Q8,Q9,Q15,Q16,Q17","IPB017N10N5LFATMA1","Package_TO_SOT_SMD:TO-263-7_TabPin4","8",""
"Q3","MMBTA92LT1G","Package_TO_SOT_SMD:SOT-23","1",""
"Q4","MMBT3906","Package_TO_SOT_SMD:SOT-23","1",""
"Q5,Q10,Q11,Q14,Q21","MMBT3904","Package_TO_SOT_SMD:SOT-23","5",""
"Q6","BSC040N10NS5ATMA1","Package_TO_SOT_SMD:TDSON-8-1","1",""
"Q12,Q22","2N7002","Package_TO_SOT_SMD:SOT-23","2",""
"Q13","BSC040N10NS5ATMA1","Package_TO_SOT_SMD:TDSON-8-1","1","DNP"
"Q18,Q19,Q20","IPB017N10N5LFATMA1","Package_TO_SOT_SMD:TO-263-7_TabPin4","3","DNP"
"R1,R2,R23,R25,R31,R32","10R","Resistor_SMD:R_0603_1608Metric","6",""
"R3","34k 1%","Resistor_SMD:R_0603_1608Metric","1",""
"R4,R12,R66","1k","Resistor_SMD:R_0603_1608Metric","3",""
"R5,R75,R85,R95,R131","22k","Resistor_SMD:R_0603_1608Metric","5",""
"R6","33k","Resistor_SMD:R_0805_2012Metric","1",""
"R7","464k","Resistor_SMD:R_0603_1608Metric","1",""
"R8","49.9k","Resistor_SMD:R_0603_1608Metric","1",""
"R9","680R 0.5W","Resistor_SMD:R_2010_5025Metric","1",""
"R10","4.7k","Resistor_SMD:R_0603_1608Metric","1",""
"R11,R14,R16,R17,R27,R67,R76,R86,R96,R129","10k","Resistor_SMD:R_0603_1608Metric","10",""
"R13,R24,R28,R37,R38,R50,R65,R71,R72,R77,R81,R82,R87,R91,R92,R97,R130,R137","100k","Resistor_SMD:R_0603_1608Metric","18",""
"R15","1.2k","Resistor_SMD:R_0603_1608Metric","1",""
"R18,R134","9.09k","Resistor_SMD:R_0603_1608Metric","2",""
"R19","499k 0.1%","Resistor_SMD:R_1206_3216Metric","1",""
"R20","604k 0.1%","Resistor_SMD:R_1206_3216Metric","1",""
"R21","51.1k 0.1%","Resistor_SMD:R_0603_1608Metric","1",""
"R22,R64","9.53M","Resistor_SMD:R_0603_1608Metric","2",""
"R26","37.4k 1%","Resistor_SMD:R_0603_1608Metric","1",""
"R29,R68,R78,R88,R138","100R","Resistor_SMD:R_0603_1608Metric","5",""
"R30","1M","Resistor_SMD:R_0603_1608Metric","1",""
"R33,R34","47k 1%","Resistor_SMD:R_1206_3216Metric","2",""
"R35,R73,R83,R93","22R","Resistor_SMD:R_0603_1608Metric","4",""
"R36","40.2k 1%","Resistor_SMD:R_0603_1608Metric","1",""
"R44","3.3k","Resistor_SMD:R_1206_3216Metric","1",""
"R45,R46","100k","Resistor_SMD:R_1206_3216Metric","2",""
"R47","33k","Resistor_SMD:R_0603_1608Metric","1",""
"R48","220k","Resistor_SMD:R_0805_2012Metric","1",""
"R49,R57","220k","Resistor_SMD:R_0603_1608Metric","2",""
"R51","470k","Resistor_SMD:R_1206_3216Metric","1",""
"R52","10k 0.75W","Resistor_SMD:R_2010_5025Metric","1",""
"R53","copper link","NetTie:NetTie-2_SMD_Pad2.0mm","1",""
"R54","2R 2512 pulse-rated 100mJ","Resistor_SMD:R_2512_6332Metric","1","DNP"
"R55,R101,R102,R107,R111,R112,R117,R121,R122,R127","100k","Resistor_SMD:R_0603_1608Metric","10","DNP"
"R56","1M","Resistor_SMD:R_0603_1608Metric","1","DNP"
"R58","47k","Resistor_SMD:R_0805_2012Metric","1",""
"R59","22R CRCW251222R0FKEGHP","Resistor_SMD:R_2512_6332Metric","1",""
"R60","220R","Resistor_SMD:R_0603_1608Metric","1",""
"R61,R62","0R","Resistor_SMD:R_0603_1608Metric","2",""
"R63","4.7k 2W","Resistor_SMD:R_2512_6332Metric","1","DNP"
"R69,R79,R89","4.64k 1%","Resistor_SMD:R_0603_1608Metric","3",""
"R70,R80,R90","20k 1%","Resistor_SMD:R_0603_1608Metric","3",""
"R74,R84,R94","10M","Resistor_SMD:R_0603_1608Metric","3",""
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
